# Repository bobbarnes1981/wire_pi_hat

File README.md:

# wire_pi_hat

https://github.com/raspberrypi/hats/blob/master/uhat-board-mechanical.pdf

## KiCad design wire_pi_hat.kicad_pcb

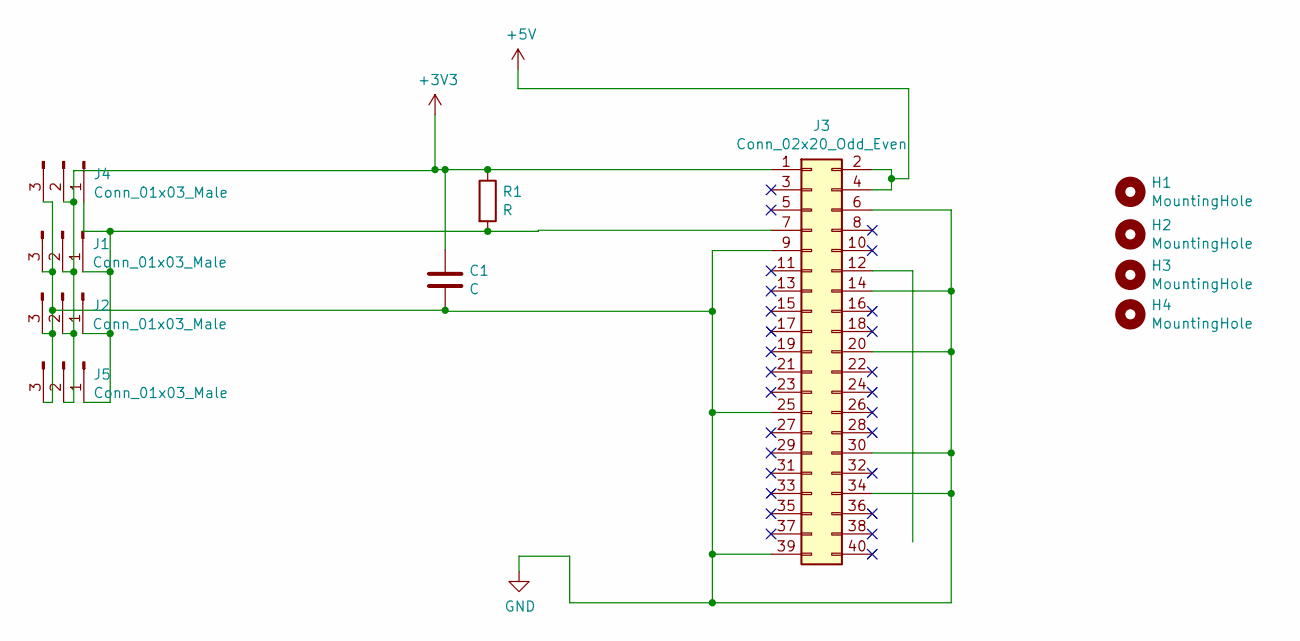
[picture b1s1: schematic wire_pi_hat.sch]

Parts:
C1: C; C_Rect_L7.2mm_W4.5mm_P5.00mm_FKS2_FKP2_MKS2_MKP2
H1, H2, H3, H4: MountingHole; MountingHole_2.7mm_M2.5_Pad
J1, J2, J4, J5: Conn_01x03_Male; TerminalBlock_Phoenix_PT-1,5-3-3.5-H_1x03_P3.50mm_Horizontal
J3: Conn_02x20_Odd_Even; PinHeader_2x20_P2.54mm_Vertical
R1: R; R_Axial_DIN0207_L6.3mm_D2.5mm_P10.16mm_Horizontal

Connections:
+3V3: C1.1, J1.2, J2.2, J3.1, J4.2, J5.2, R1.1
+5V: J3.2, J3.4
GND: C1.2, J1.3, J2.3, J3.6, J3.9, J3.14, J3.20, J3.25, J3.30, J3.34, J3.39, J4.3, J5.3
unnamed: J1.1, J2.1, J3.7, J4.1, J5.1, R1.2

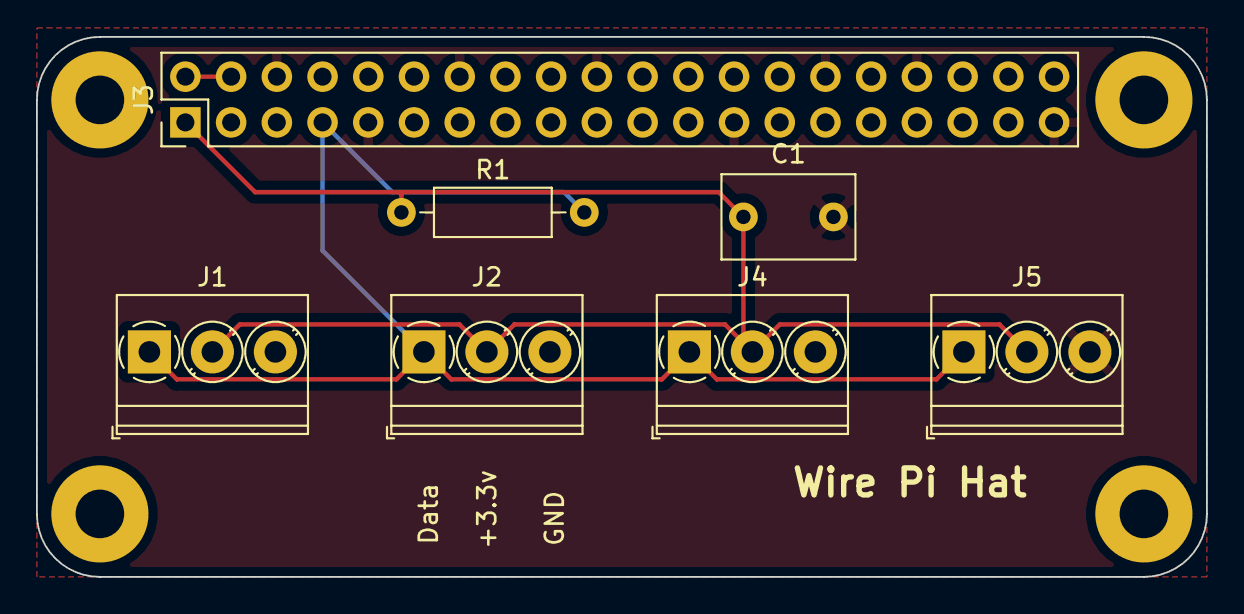
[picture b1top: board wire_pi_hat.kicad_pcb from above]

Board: 2 copper layers, 65.0 x 30.0 mm, 11 parts (0 on the bottom side), 4 nets.

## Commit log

2022-03-17 Add gerbers
